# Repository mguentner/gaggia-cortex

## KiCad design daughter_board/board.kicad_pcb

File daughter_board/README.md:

# ESP32 Daughter Board

This is intended for an ESP32 board with an onboard AC/DC power supply
and a relais for that can be used to power the coffee machine itself.

[Example offering on Aliexpress](https://www.aliexpress.us/item/3256805662668563.html) for the main board.

## Required Parts

* 1 x Mainboard
* 1 x WAGO 233-506 Terminal Block
* 1 x MAX31855 temperature sensor
* 1 x K-Type Thermocouple
* 1 x 100nF capacitor (see MAX31855 datasheet)

## Images

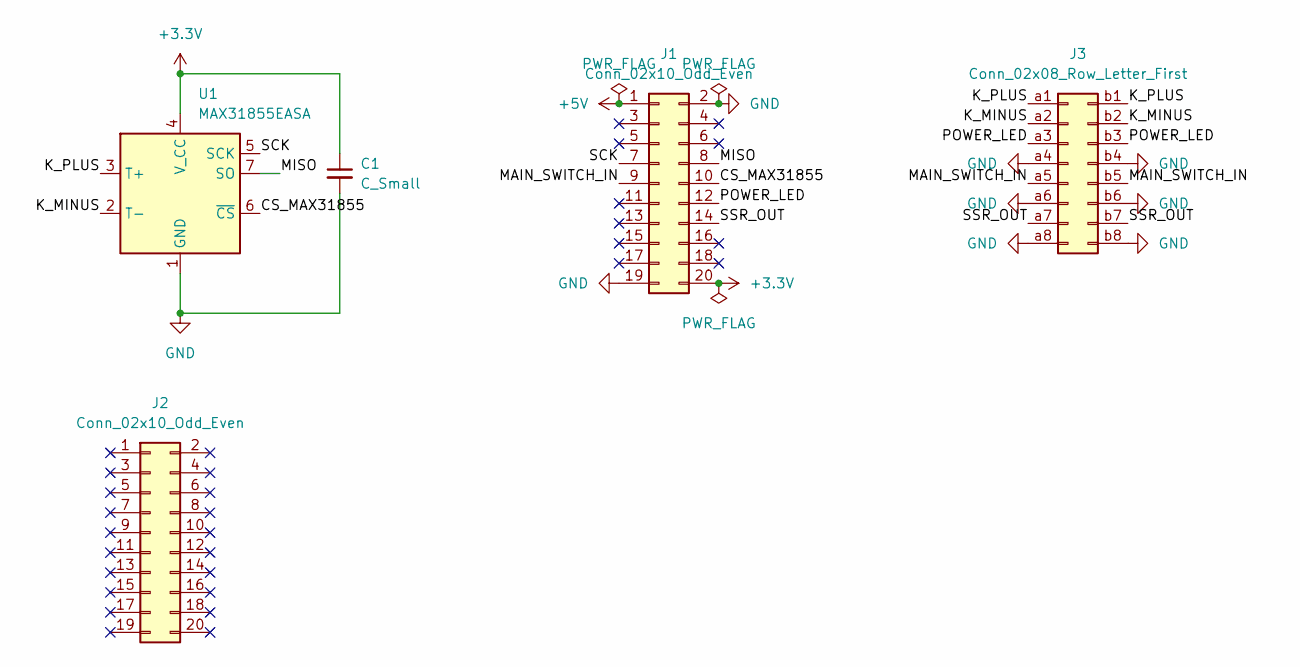
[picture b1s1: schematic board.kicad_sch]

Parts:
C1: C_Small; C_0603_1608Metric
J1, J2: Conn_02x10_Odd_Even; PinHeader_2x10_P2.54mm_Vertical
J3: Conn_02x08_Row_Letter_First; con-wago-233-508
U1: MAX31855EASA; SOIC-8_3.9x4.9mm_P1.27mm

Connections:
+3.3V: C1.1, J1.20, U1.4 (V_CC)
+5V: J1.1
/CS_MAX31855: J1.10, U1.6 (~CS)
/K_MINUS: J3.a2, J3.b2, U1.2 (T-)
/K_PLUS: J3.a1, J3.b1, U1.3 (T+)
/MAIN_SWITCH_IN: J1.9, J3.a5, J3.b5
/MISO: J1.8, U1.7 (SO)
/POWER_LED: J1.12, J3.a3, J3.b3
/SCK: J1.7, U1.5 (SCK)
/SSR_OUT: J1.14, J3.a7, J3.b7
GND: C1.2, J1.2, J1.19, J3.a4, J3.a6, J3.a8, J3.b4, J3.b6, J3.b8, U1.1 (GND)

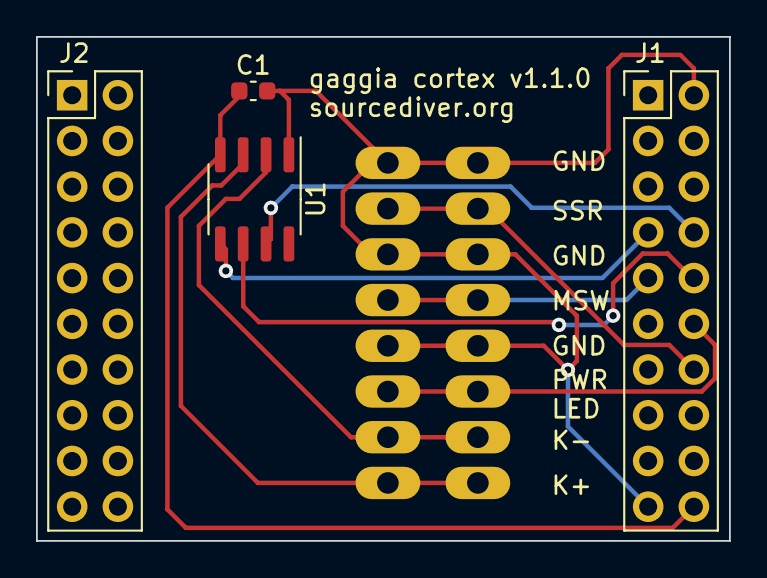
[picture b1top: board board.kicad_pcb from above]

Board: 2 copper layers, 38.5 x 28.0 mm, 5 parts (1 on the bottom side), 10 nets.

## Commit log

2024-01-12 add daughter board schematics
2024-01-12 add README for daughter board
2024-01-12 add mainboard requirement
2024-03-08 split config into base and switch/button files
2024-03-08 add README.md
2024-03-08 add case freecad file and .stl
2024-03-08 correct mount, add ssr cover
2024-03-08 fix: add/enable captive portal if wifi connect fails
